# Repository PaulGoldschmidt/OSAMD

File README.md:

# Wie man ein Luftqualitätssensor mit einem niedrigen Budget baut: Das OSAMD-Projekt

Hohe Luftqualität ist wichtig. Eigentlich schon immer, denn in besserer Luft kann man sich länger konzentrieren. Grade in der Schule ist das Thema doch jetzt wichtiger denn je, denn dank COVID-19 müssen in vielen Schulen Deutschlands regelmäßig Lüftungspausen eingelegt werden. Was ansich gut ist, wird im Winter von Tag zu Tag schwieriger umzusetzen: Das kalte Klima und die Heizungen im Klassenzimmer führen so täglich einen Kampf um die Lufttemperatur, bei der die Heizung nur unter erheblicher Wärmeabgabe die Luft aufwärmen kann, was zu enormen Steigerungen der Heizungskosten und einem erhöhtem CO2-Ausstoß führt.

Deshalb habe ich mich dafür entschlossen, ein Luftqualitätsmessgerät zu entwickeln, welches mit niedrigen Teilkosten (circa 7-10 Euro/Einheit) die Luft in Klassenzimmern überwachen kann und eine Warnung abgibt, wenn die Luftqualität kritisch schlecht ist. Der Name dieses Projekts, OSAMD, steht für "Open-Source Air-Monitoring Device", also eine quelloffene Lösung zur Überwachung der Luftqualität.
Eine Anleitung zum Selbstbau dieses Projekts liegt im Ordner "0_Documentation", die Hardwareteile im Ordner "1_Hardware" und die benötigte Software im Ordner "2_Software".

[So wurde übrigens das Gehäuse designed](https://www.youtube.com/watch?v=d4DvKm7_OzI)

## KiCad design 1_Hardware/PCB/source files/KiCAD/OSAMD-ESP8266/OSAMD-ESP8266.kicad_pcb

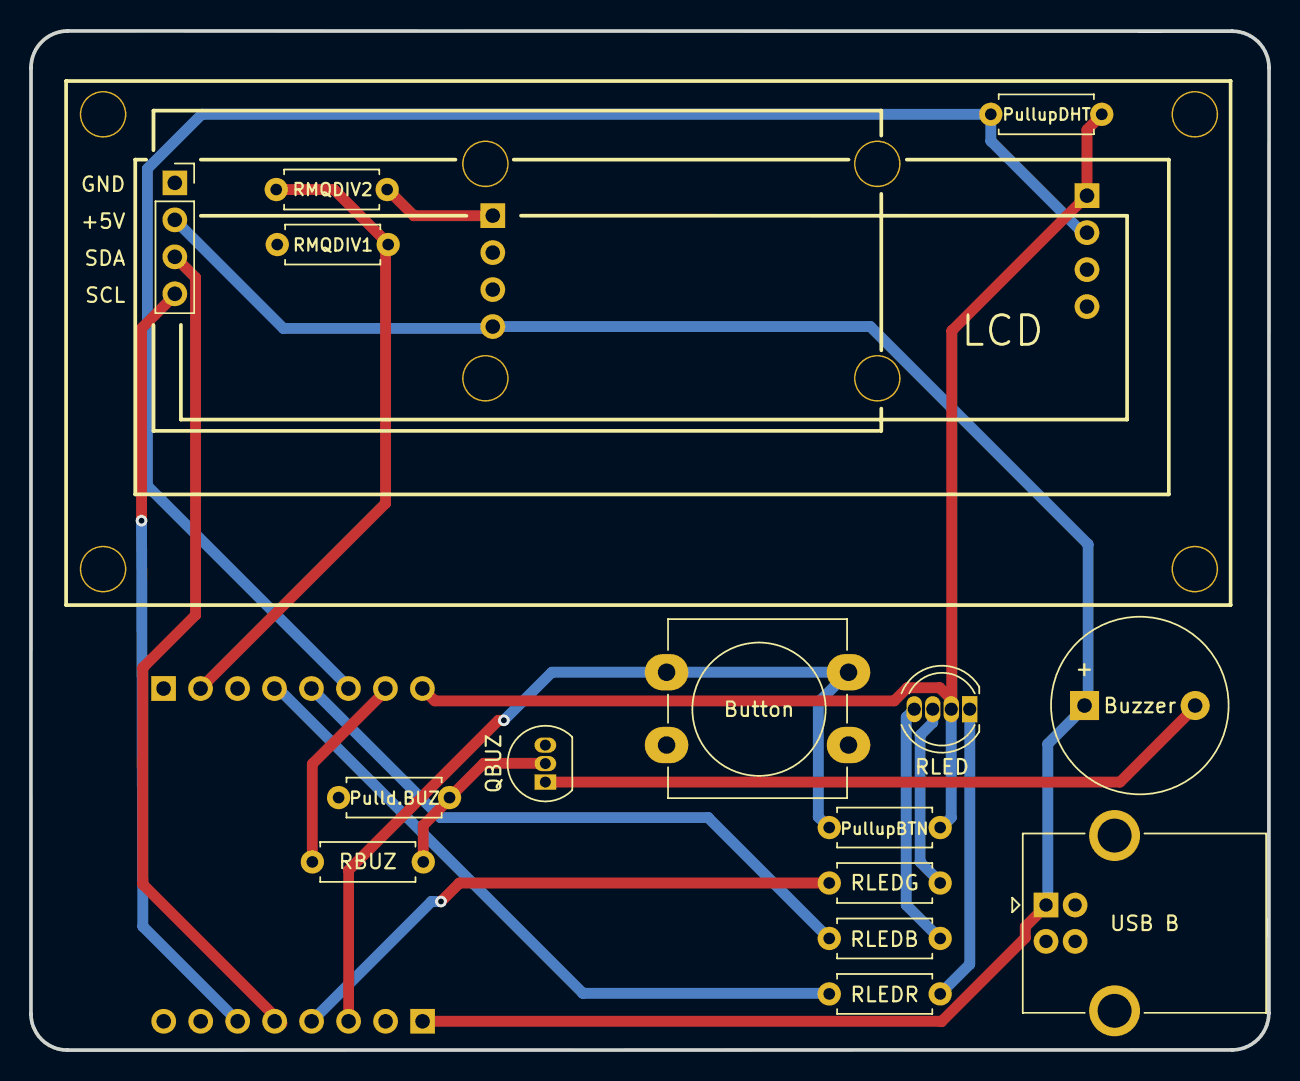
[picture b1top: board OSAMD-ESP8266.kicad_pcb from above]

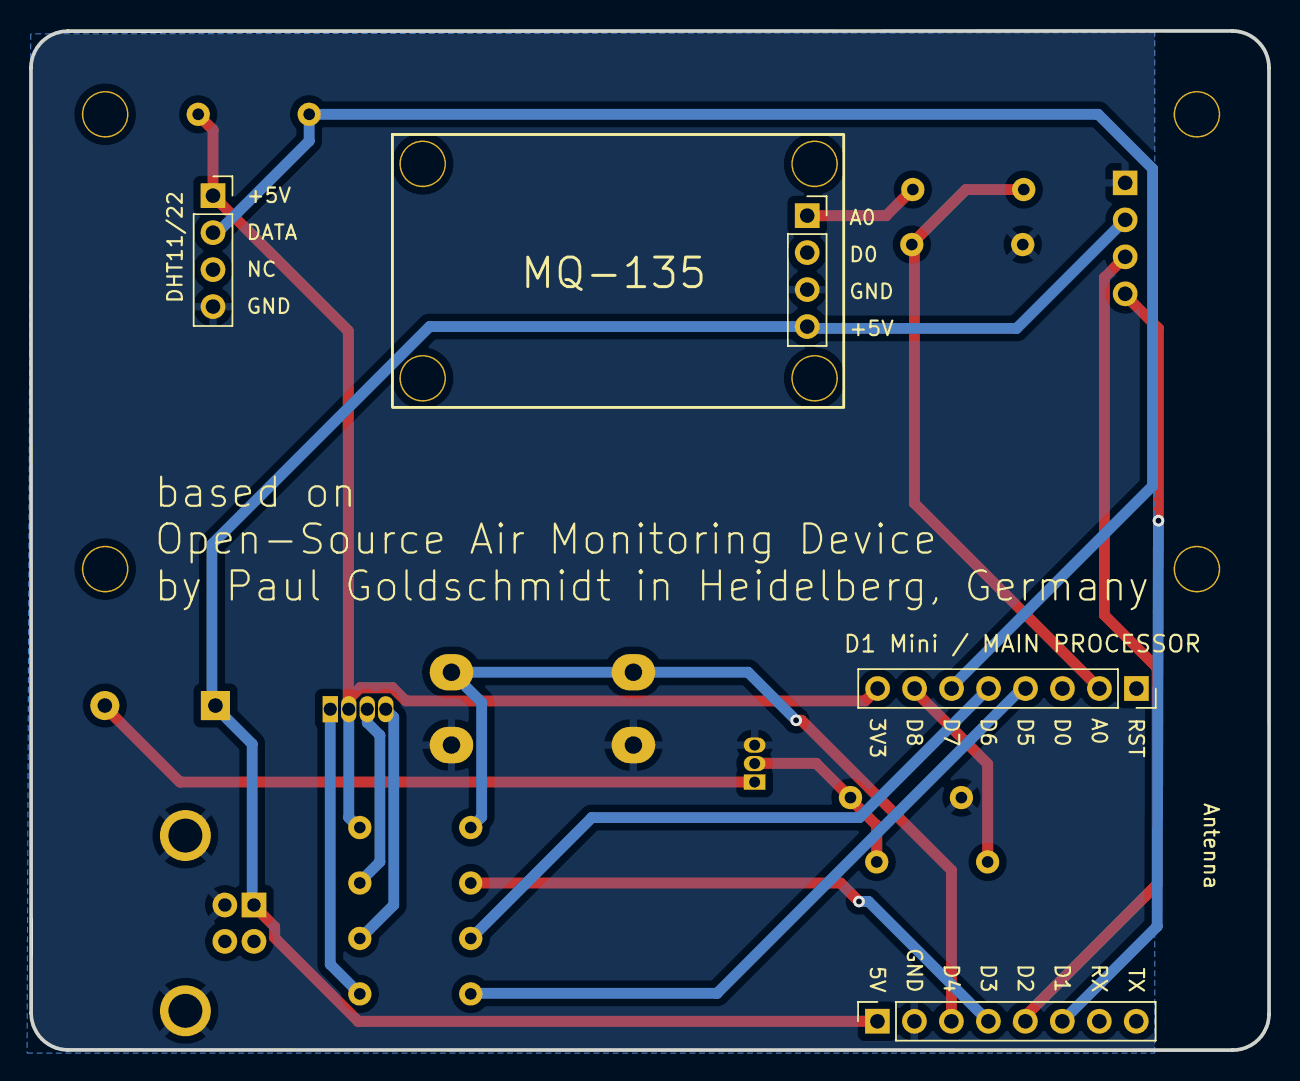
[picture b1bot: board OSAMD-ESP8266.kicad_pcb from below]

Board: 2 copper layers, 85.1 x 70.0 mm, 21 parts (4 on the bottom side), 18 nets.

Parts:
Button: SW_Pushbutton; SW_PUSH-12mm_Wuerth-430476085716
Buzzer: Buzzer 5V 30mA; Buzzer_12x9.5RM7.6
J1: DHT-Socket; PinSocket_1x04_P2.54mm_Vertical
J2: MQ-135 Conn; PinSocket_1x04_P2.54mm_Vertical
J3: LCD Conn; PinSocket_1x04_P2.54mm_Vertical
J7: Socket_D1_Mini_01_08; PinSocket_1x08_P2.54mm_Vertical
J8: Socket_D1_Mini_09_16; PinSocket_1x08_P2.54mm_Vertical
Pulld.BUZ: 10k; R_Axial_DIN0207_L6.3mm_D2.5mm_P7.62mm_Horizontal
PullupBTN: 10k; R_Axial_DIN0207_L6.3mm_D2.5mm_P7.62mm_Horizontal
PullupDHT: 10k; R_Axial_DIN0207_L6.3mm_D2.5mm_P7.62mm_Horizontal
QBUZ: BC547; TO-92_Inline
RBUZ: 1k; R_Axial_DIN0207_L6.3mm_D2.5mm_P7.62mm_Horizontal
RLED: LED_RAGB; LED_D5.0mm-4_RGB
RLEDB: 120R; R_Axial_DIN0207_L6.3mm_D2.5mm_P7.62mm_Horizontal
RLEDG: 130R; R_Axial_DIN0207_L6.3mm_D2.5mm_P7.62mm_Horizontal
RLEDR: 180R; R_Axial_DIN0207_L6.3mm_D2.5mm_P7.62mm_Horizontal
RMQDIV1: 3k; R_Axial_DIN0207_L6.3mm_D2.5mm_P7.62mm_Horizontal
RMQDIV2: 2k; R_Axial_DIN0207_L6.3mm_D2.5mm_P7.62mm_Horizontal
S1: MQ-135
U1: LCD; 1602 LCD IIC
USB B: USB_B; USB_B_OST_USB-B1HSxx_Horizontal

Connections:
+5V: Buzzer.1 (-), J2.4, J3.2, J8.1, USB B.1 (VBUS)
/+3V3: J1.1, J7.8, PullupBTN.1, PullupDHT.1, RLED.2 (A)
/A0 MQ-135: J7.2, RMQDIV1.2, RMQDIV2.1
/BLUE: RLED.4 (BK), RLEDB.2
/BTN: Button.1, J8.3, PullupBTN.2
/BUZBASE: Pulld.BUZ.2, QBUZ.2 (B), RBUZ.2
/BUZCOL: Buzzer.2 (+), QBUZ.1 (C)
/BUZZER: J7.7, RBUZ.1
/DHT Data: J1.2, J7.6, PullupDHT.2
/GREEN: RLED.3 (GK), RLEDG.2
/LCD_SCL: J3.4, J8.6
/LCD_SDA: J3.3, J8.5
/LED B: J7.5, RLEDB.1
/LED G: J8.4, RLEDG.1
/LED R: J7.4, RLEDR.1
/MQ-135 A0: J2.1, RMQDIV2.2
/RED: RLED.1 (RK), RLEDR.2
GND: Button.2, J1.4, J2.3, J3.1, J8.2, Pulld.BUZ.1, QBUZ.3 (E), RMQDIV1.1, USB B.4 (GND), USB B.5 (Shield)

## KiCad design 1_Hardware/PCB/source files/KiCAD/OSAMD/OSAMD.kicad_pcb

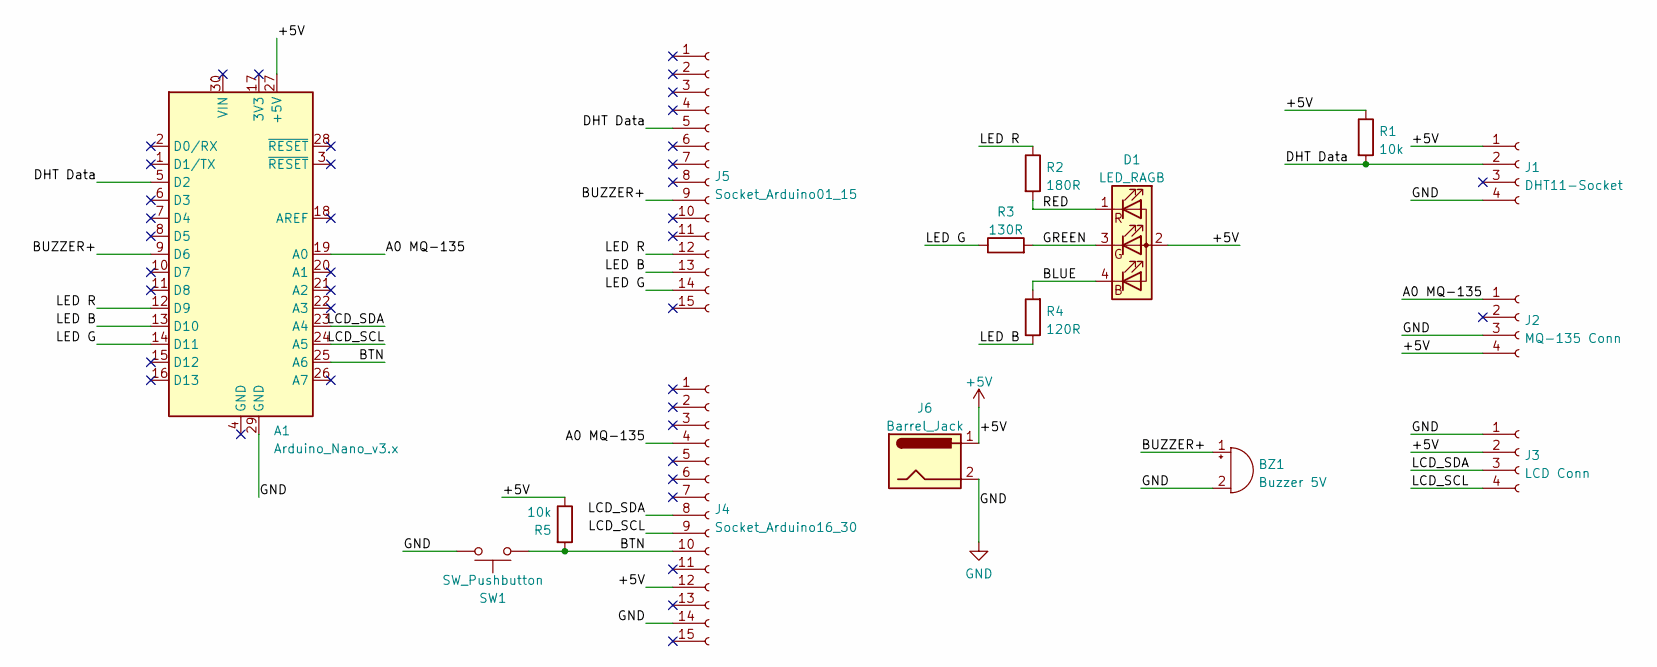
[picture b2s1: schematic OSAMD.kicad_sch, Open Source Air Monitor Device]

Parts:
A1: Arduino_Nano_v3.x; Arduino_Nano
BZ1: Buzzer 5V; Buzzer_12x9.5RM7.6
D1: LED_RAGB; LED_D5.0mm-4_RGB
J1: DHT11-Socket; PinSocket_1x04_P2.54mm_Vertical
J2: MQ-135 Conn; PinSocket_1x04_P2.54mm_Vertical
J3: LCD Conn; PinSocket_1x04_P2.54mm_Vertical
J4: Socket_Arduino16_30; PinSocket_1x15_P2.54mm_Vertical
J5: Socket_Arduino01_15; PinSocket_1x15_P2.54mm_Vertical
J6: Barrel_Jack; BarrelJack_Wuerth_6941xx301002
R1, R5: 10k; R_Axial_DIN0207_L6.3mm_D2.5mm_P10.16mm_Horizontal
R2: 180R; R_Axial_DIN0207_L6.3mm_D2.5mm_P10.16mm_Horizontal
R3: 130R; R_Axial_DIN0207_L6.3mm_D2.5mm_P10.16mm_Horizontal
R4: 120R; R_Axial_DIN0207_L6.3mm_D2.5mm_P10.16mm_Horizontal
SW1: SW_Pushbutton; SW_PUSH-12mm_Wuerth-430476085716

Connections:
+5V: A1.27 (+5V), D1.2 (A), J1.1, J2.4, J3.2, J4.12, J6.1, R1.1, R5.1
/A0 MQ-135: A1.19 (A0), J2.1, J4.4
/BLUE: D1.4 (BK), R4.2
/BTN: A1.25 (A6), J4.10, R5.2, SW1.1
/BUZZER+: A1.9 (D6), BZ1.1 (-), J5.9
/DHT Data: A1.5 (D2), J1.2, J5.5, R1.2
/GREEN: D1.3 (GK), R3.2
/LCD_SCL: A1.24 (A5), J3.4, J4.9
/LCD_SDA: A1.23 (A4), J3.3, J4.8
/LED B: A1.13 (D10), J5.13, R4.1
/LED G: A1.14 (D11), J5.14, R3.1
/LED R: A1.12 (D9), J5.12, R2.1
/RED: D1.1 (RK), R2.2
GND: A1.29 (GND), BZ1.2 (+), J1.4, J2.3, J3.1, J4.14, J6.2, SW1.2

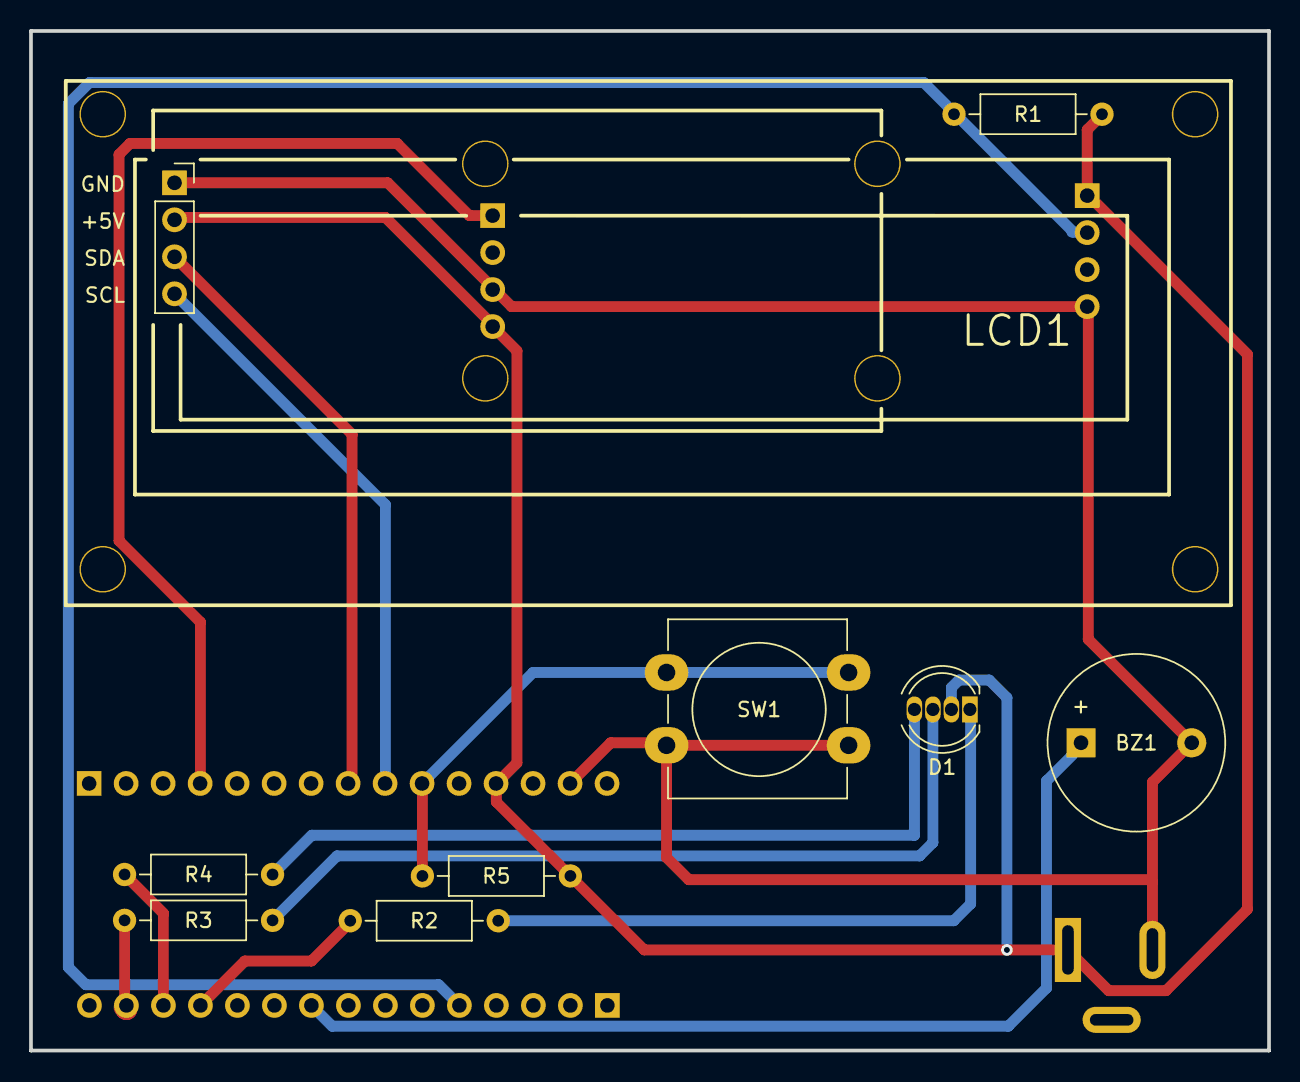
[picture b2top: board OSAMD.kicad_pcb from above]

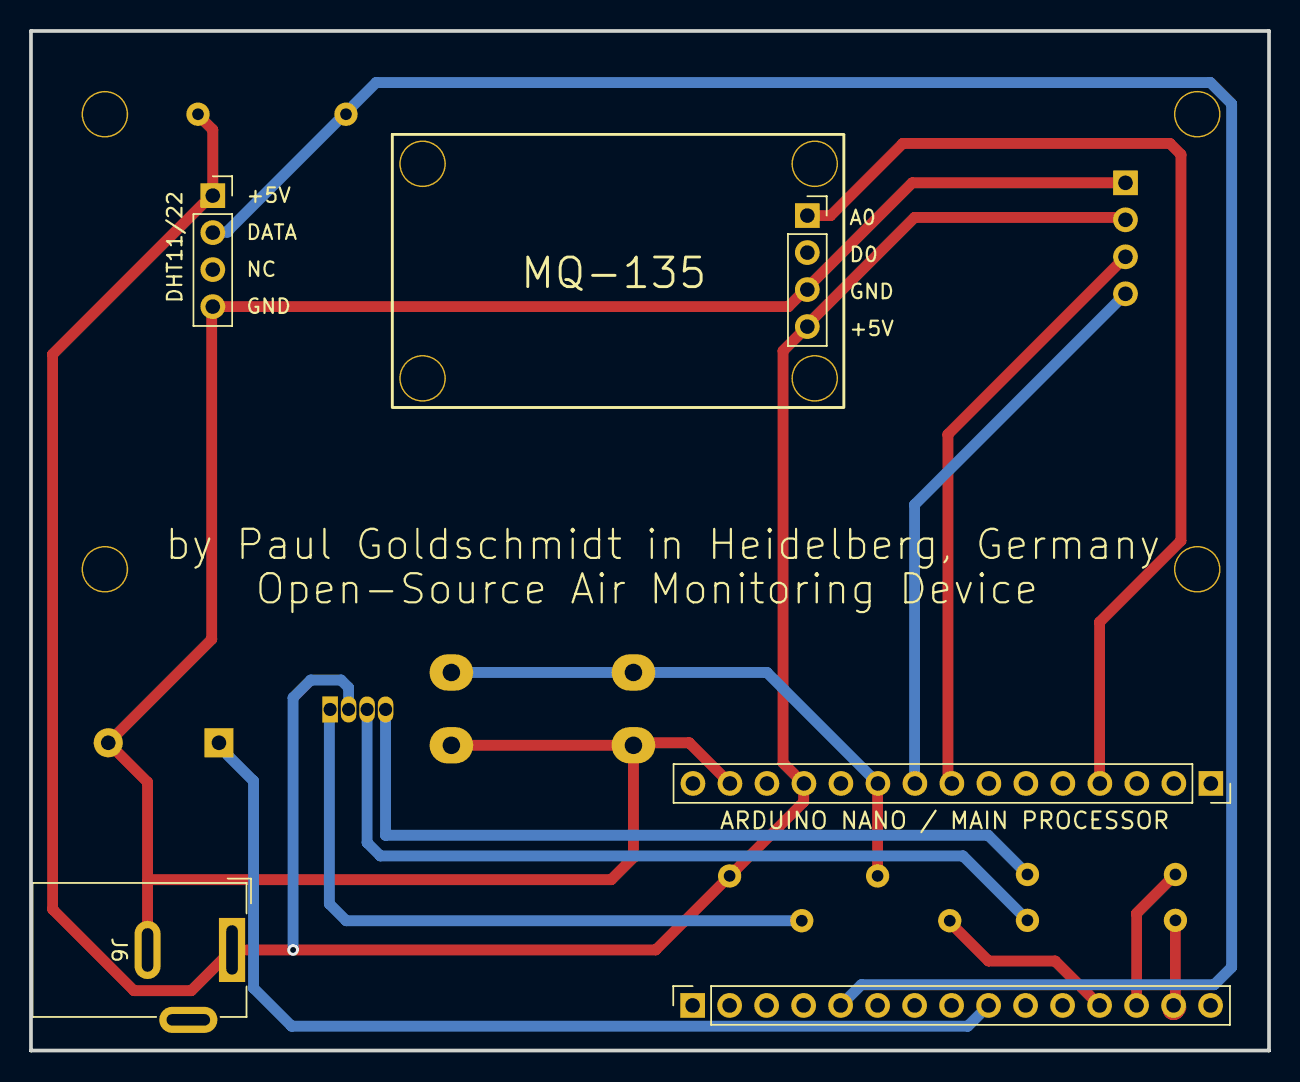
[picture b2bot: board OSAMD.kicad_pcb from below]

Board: 2 copper layers, 85.0 x 70.0 mm, 16 parts (5 on the bottom side), 14 nets.

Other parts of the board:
S1: MQ-135
U1: LCD1; 1602 LCD IIC

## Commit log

2020-10-28 Created Readme.txt, added basic project details
2020-10-28 Created building instructions
2020-10-31 created first test
2020-11-08 Added two more tests
2020-11-08 Added Delay and removed unnecessary comments
2020-11-08 Added main.ino
2020-11-09 Small corrections in tabulation
2020-11-26 LED-Test hinzugefügt und weitere Fortschritte im Hauptprogramm
2020-11-26 Vorheizroutine hinzugefügt
2020-11-26 Prozessleiste bug behoben und Prozentanzeige für Vorheitzen hinzugefügt
2020-11-26 Die Vorwärmroutine ist fertiggestellt
2020-11-27 Viele Verbesserungen im Code sowie neustrukturierungen
2020-11-27 Begonnen, die Hauptschleife auszuarbeiten
2020-11-27 Hauptschleife weitergebaut, Menü fehlt noch komplett
2020-11-27 Alarmstufe Rot piepst jetzt zwei mal
2020-11-28 Menü wurde angefangen
2020-11-28 Umlaute hinzugefügt (Kodiert als z.B. \365) und weitere Menüausarbeitung
2020-11-28 Menü leicht verbessert
2020-11-29 Weitere Menüverbesserungen, Bugs behoben in der Hauptschleife
2020-11-29 EEPROM-Speicherung hinzugefügt.
2020-11-29 Zweites Menü eingefügt, Fehlerbehebungen und früheres Einlesen von den Variablen
2020-11-29 Fehlerbehebungen
    Einen Fehler behoben, bei dem der Buzzer trotz Stummschaltung noch gepiepst hat.
2020-12-06 PCB-Dateien hinzugefügt
2020-12-06 STL-Gehäusedateien Hinzugefügt
    Version 2.0 der Dateien
2020-12-06 Bauanleitung hinzugefügt
2020-12-06 BOM Added.
2020-12-06 Stromkabel auf BOM hinzugefügt
2020-12-06 zwei Bilder hinzugefügt.
2020-12-06 Bauanleitung ergänzt.
2020-12-06 Bilder hinzugefüt und Prozentwerte im Hauptprogramm verändert
2020-12-06 sehr viele Bilder hinzugefügt.
2020-12-06 Weiter an der Doku geschrieben
2020-12-06 Bild des Knopfes hinzugefügt.
2020-12-06 Bauanleitung feriggestellt
2020-12-06 Bauanleitung Bild hinzugefügt
2020-12-06 Rechtschreibfehler korrigiert und Bild hinzugefügt.
2020-12-06 Video in die Readme hinzugefügt.
2020-12-06 fehlerhafter Link behoben.
2020-12-29 Typo Fix
2021-01-27 Specified readme, fixed typo
2021-03-31 Kleine Typingfixes und eine spezifizierung der LED-Position
    Danke an @AlexWerz für den Hinweis der ungenauen LED-Beschreibung!
2021-03-31 Reverted progress bar (bad air is smaller bar), raised the max value to 768, commented about the lib used for LCD, change lcd.begin to lcd.init
2021-03-31 Hinweis auf ältere Hardwareversion hinzugefügt
2021-04-01 Neue PCB Version 2.1
    Es wurde verbessert, wie der Kontrast des Displays eingestellt werden kann: Jetzt gibt es ein Loch durch die Leiterplatte, mit dem auch bei verlötetem Display der Kontrast nachgestellt werden kann.
2021-04-01 Dateinamen vereinheitlicht
2023-01-04 started implementation of DHT temperature sensor series, version bump
2023-01-04 first (wanky) implementation of dht sensor
2023-01-04 Stable implementation of DHT Temperature probe, general bugfixes & more documentation :100:
2023-01-04 added pcb source files for issue #2
2023-01-08 Hotfix fixing non-display on tempprobe not connected
2023-01-09 KiCAD backup folders
2023-01-09 reverse engineered schematics in KiCAD
2023-01-09 linting, relative links
2023-01-09 linting, relative links (2)
2023-01-09 d'oh
2023-01-09 d'oh (2)
2023-01-12 (NOT WORKING) Lib switch
    Mayor changes in measurement approach, does currently not work.
2023-01-15 added Wemos D1 Mini variant
2023-01-15 first tiny step towards ESP8266
2023-04-28 ignore KiCad and Arduino IDE 2.x artifacts
2023-04-28 documentation of the "menu tree" (in yed and pdf)
2023-04-28 typo
2023-04-28 complete rewrite including code for ESP32 and ESP8266
2023-04-28 switched button and buzzer pin
2023-04-28 ignore all local KiCad and notepad++ backups
2023-08-06 added missing header file
2023-08-06 setting config option is not supposed to return anything
2023-08-06 ignore VSCode settings, gerber files, KiCad lock-files
2023-08-06 rounded edges on the pcb set gerber settings for jlcpcb
2023-08-06 added option to toggle LED
2023-08-06 renamed methods that only change the state of the LED hardware
2023-08-06 fixed const methods
2023-08-06 indentation, comments, small fixes
